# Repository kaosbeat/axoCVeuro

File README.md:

# axoCVeuro

# BOM
https://www.digikey.be/product-detail/en/e-switch/100SP1T1B4M2QE/EG2355-ND/378824

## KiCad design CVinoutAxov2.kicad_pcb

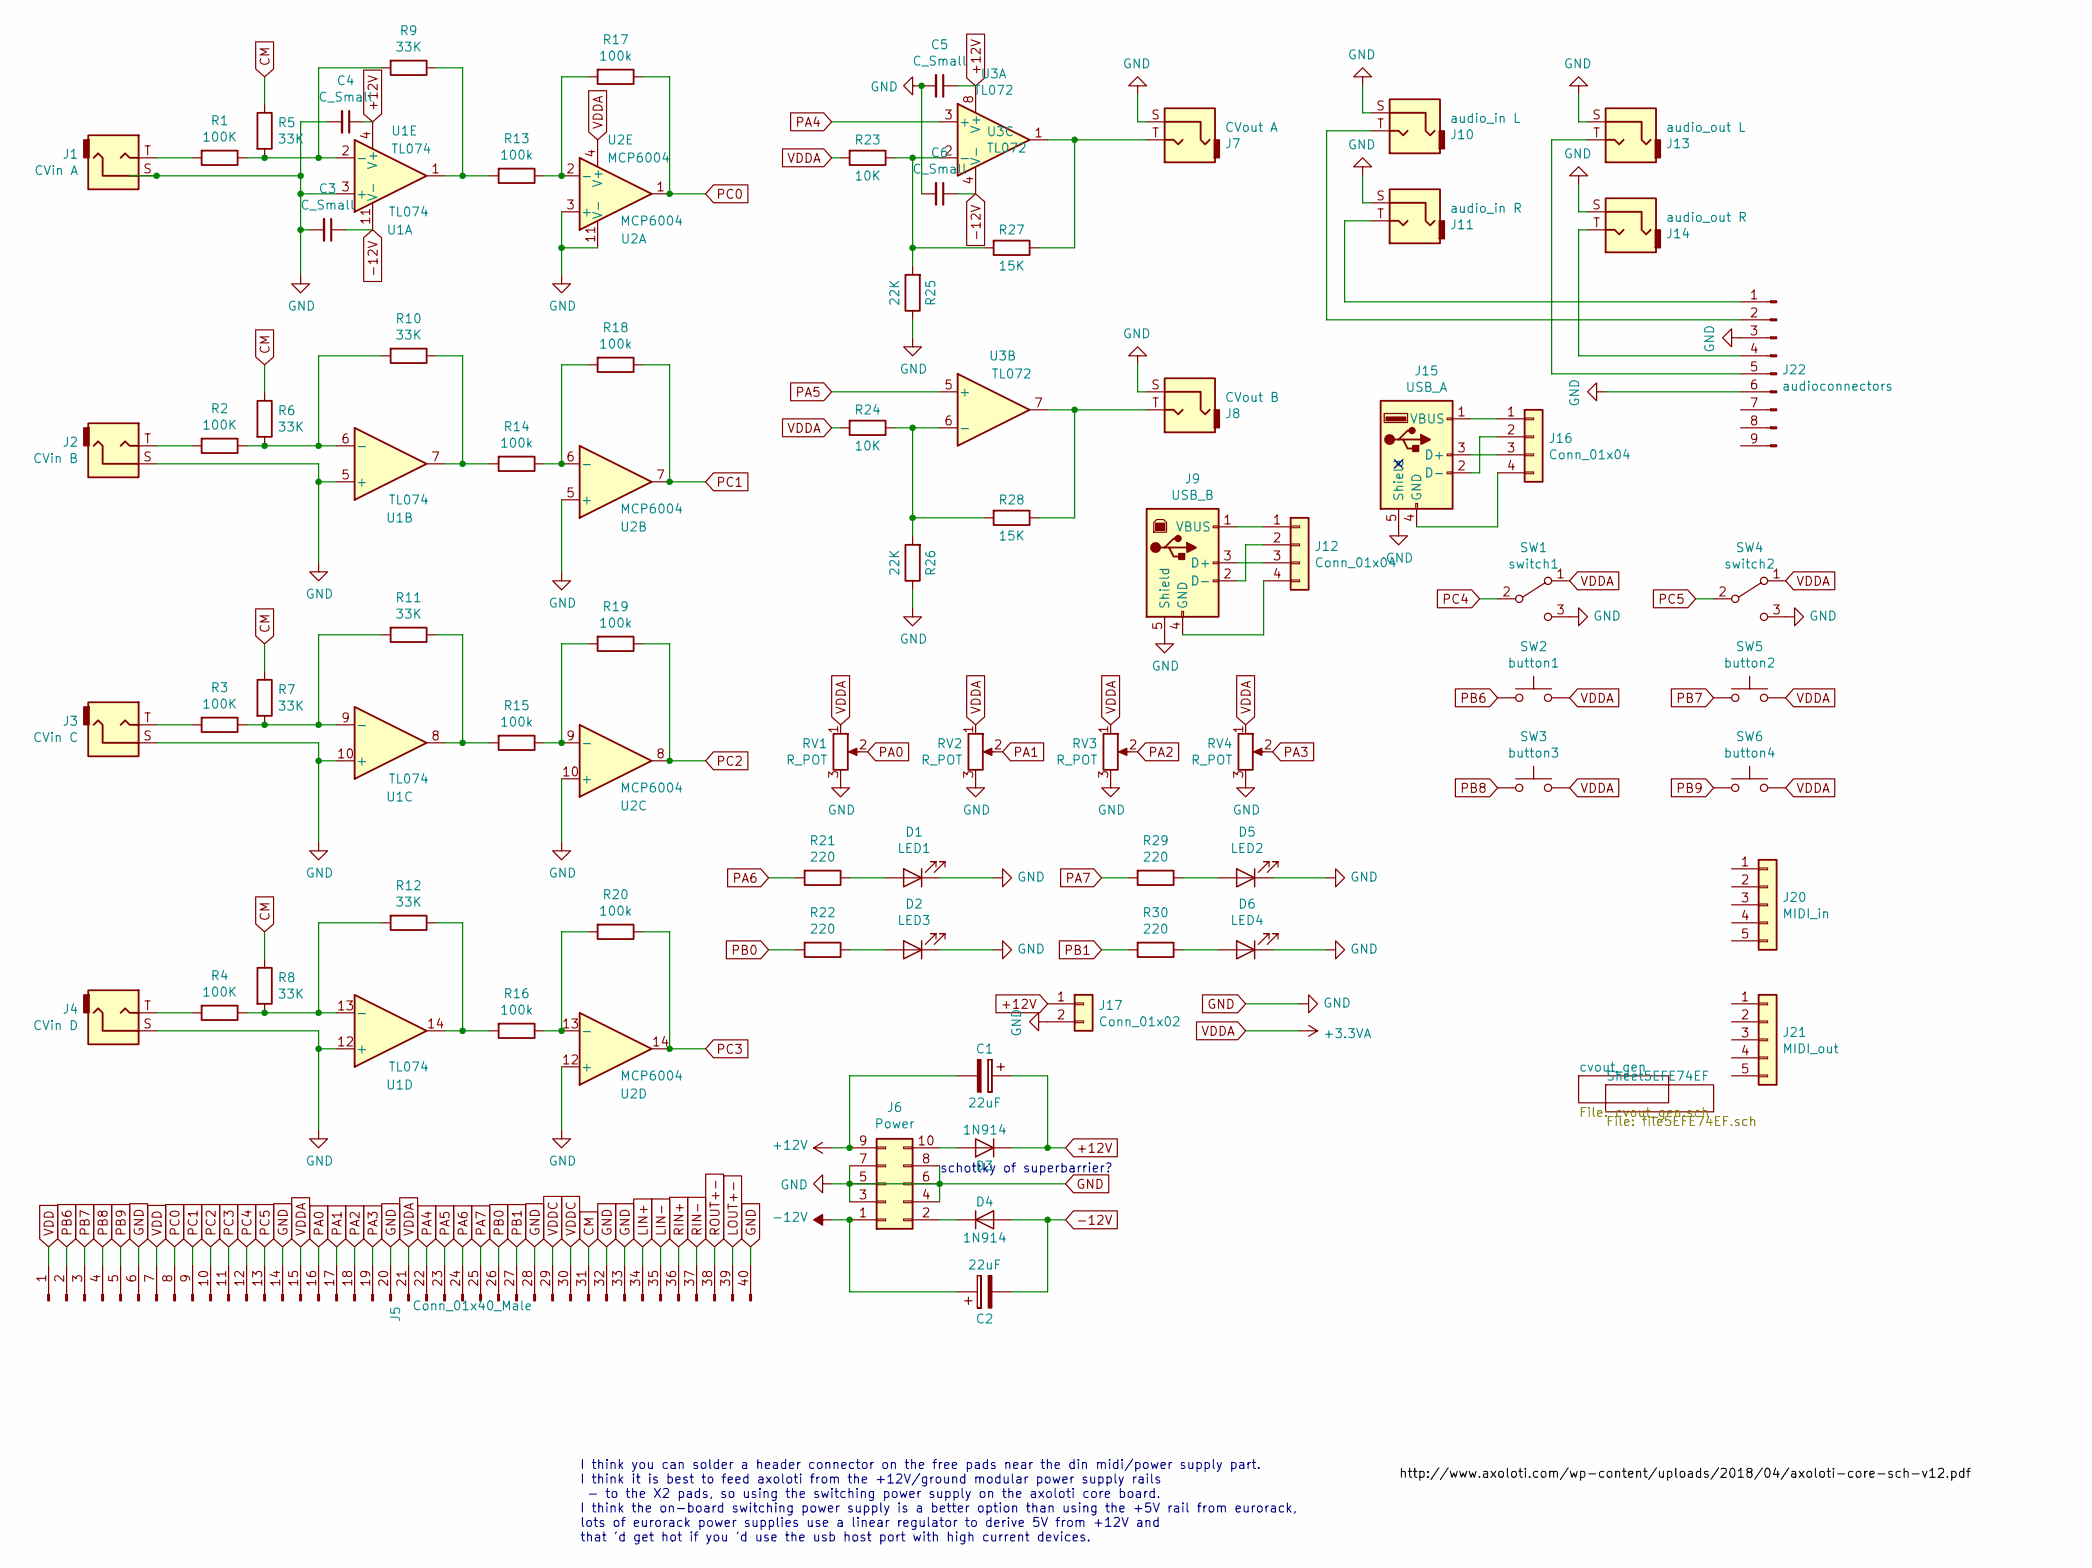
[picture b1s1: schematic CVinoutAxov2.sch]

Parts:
C1, C2: 22uF; CP_Radial_D5.0mm_P2.50mm
C3, C4, C5, C6: C_Small; C_Disc_D5.0mm_W2.5mm_P2.50mm
D1: LED1; LED_D5.0mm
D2: LED3; LED_D5.0mm
D3, D4: 1N914; D_DO-35_SOD27_P7.62mm_Horizontal
D5: LED2; LED_D5.0mm
D6: LED4; LED_D5.0mm
J1: CVin A; Jack_3.5mm_QingPu_WQP-PJ398SM_Vertical_CircularHoles
J2: CVin B; Jack_3.5mm_QingPu_WQP-PJ398SM_Vertical_CircularHoles
J3: CVin C; Jack_3.5mm_QingPu_WQP-PJ398SM_Vertical_CircularHoles
J4: CVin D; Jack_3.5mm_QingPu_WQP-PJ398SM_Vertical_CircularHoles
J5: Conn_01x40_Male; PinHeader_1x40_P2.54mm_Vertical
J6: Power; IDC-Header_2x05_P2.54mm_Vertical
J7: CVout A; Jack_3.5mm_QingPu_WQP-PJ398SM_Vertical_CircularHoles
J8: CVout B; Jack_3.5mm_QingPu_WQP-PJ398SM_Vertical_CircularHoles
J9: USB_B; USB_B_Amphenol_MUSB-D511_Vertical_Rugged
J10: audio_in L; Jack_3.5mm_QingPu_WQP-PJ398SM_Vertical_CircularHoles
J11: audio_in R; Jack_3.5mm_QingPu_WQP-PJ398SM_Vertical_CircularHoles
J12: Conn_01x04; PinHeader_1x04_P2.54mm_Vertical
J13: audio_out L; Jack_3.5mm_QingPu_WQP-PJ398SM_Vertical_CircularHoles
J14: audio_out R; Jack_3.5mm_QingPu_WQP-PJ398SM_Vertical_CircularHoles
J15: USB_A; USB-A-S-VT
J16: Conn_01x04; JST_EH_B04B-EH-A_1x04_P2.50mm_Vertical
J17: Conn_01x02; JST_EH_B02B-EH-A_1x02_P2.50mm_Vertical
J20: MIDI_in; PinHeader_1x05_P2.54mm_Vertical
J21: MIDI_out; PinHeader_1x05_P2.54mm_Vertical
J22: audioconnectors; PinHeader_1x09_P2.54mm_Vertical
R1, R2, R3, R4: 100K; R_Axial_DIN0207_L6.3mm_D2.5mm_P10.16mm_Horizontal
R5, R6, R7, R8, R9, R10, R11, R12: 33K; R_Axial_DIN0207_L6.3mm_D2.5mm_P10.16mm_Horizontal
R13, R14, R15, R16, R17, R18, R19, R20: 100k; R_Axial_DIN0207_L6.3mm_D2.5mm_P10.16mm_Horizontal
R21, R22, R29, R30: 220; R_Axial_DIN0207_L6.3mm_D2.5mm_P10.16mm_Horizontal
R23, R24: 10K; R_Axial_DIN0207_L6.3mm_D2.5mm_P10.16mm_Horizontal
R25, R26: 22K; R_Axial_DIN0207_L6.3mm_D2.5mm_P10.16mm_Horizontal
R27, R28: 15K; R_Axial_DIN0207_L6.3mm_D2.5mm_P10.16mm_Horizontal
RV1, RV2, RV3, RV4: R_POT; Potentiometer_Alps_RK09K_Single_Vertical
SW1: switch1; E-switch_SPDT_100SP1T1B4M2QE
SW2: button1; Push_E-Switch_KS01Q01
SW3: button3; Push_E-Switch_KS01Q01
SW4: switch2; E-switch_SPDT_100SP1T1B4M2QE
SW5: button2; Push_E-Switch_KS01Q01
SW6: button4; Push_E-Switch_KS01Q01
U1: TL074; SMDIP-14_W9.53mm
U2: MCP6004; SMDIP-14_W9.53mm
U3: TL072; SMDIP-8_W9.53mm

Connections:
+12V: C1.1, C1.2, C4.1, C5.1, D3.1 (K), J6.9, J17.1, U1.4 (V+), U3.8 (V+)
-12V: C2.1, C2.2, C3.1, C6.1, D4.2 (A), J6.1, U1.11 (V-), U3.4 (V-)
CM: J5.31, R5.1, R6.1, R7.1, R8.1
GND: C3.2, C4.2, C5.2, C6.2, D1.1 (K), D2.1 (K), D5.1 (K), D6.1 (K), J1.S, J2.S, J3.S, J4.S, J5.6, J5.14, J5.20, J5.28, J5.32, J5.33, J5.40, J6.3, J6.4, J6.5, J6.6, J6.7, J6.8, J7.S, J8.S, J9.5 (Shield), J10.S, J11.S, J13.S, J14.S, J15.5 (Shield), J17.2, J22.3, J22.6, R25.1, R26.1, RV1.3, RV2.3, RV3.3, RV4.3, SW1.3 (C), SW4.3 (C), U1.3 (+), U1.5 (+), U1.10 (+), U1.12 (+), U2.3 (+), U2.5 (+), U2.10 (+), U2.11 (V-), U2.12 (+)
LIN+: J5.34
LIN-: J5.35
LOUT+-: J5.39
unnamed: D1.2 (A), R21.1
unnamed: D2.2 (A), R22.1
unnamed: D3.2 (A), J6.10
unnamed: D4.1 (K), J6.2
unnamed: D5.2 (A), R29.1
unnamed: D6.2 (A), R30.1
unnamed: J1.T, R1.2
unnamed: J2.T, R2.2
unnamed: J3.T, R3.2
unnamed: J4.T, R4.2
unnamed: J7.T, R27.1, U3.1
unnamed: J8.T, R28.1, U3.7
unnamed: J10.T, J22.2
unnamed: J11.T, J22.1
unnamed: J9.1 (VBUS), J12.1
unnamed: J9.2 (D-), J12.2
unnamed: J9.3 (D+), J12.3
unnamed: J9.4 (GND), J12.4
unnamed: J13.T, J22.5
unnamed: J14.T, J22.4
unnamed: J15.1 (VBUS), J16.1
unnamed: J15.2 (D-), J16.2
unnamed: J15.3 (D+), J16.3
unnamed: J15.4 (GND), J16.4
unnamed: R1.1, R5.2, R9.2, U1.2 (-)
unnamed: R10.1, R14.2, U1.7
unnamed: R2.1, R6.2, R10.2, U1.6 (-)
unnamed: R11.1, R15.2, U1.8
unnamed: R3.1, R7.2, R11.2, U1.9 (-)
unnamed: R12.1, R16.2, U1.14
unnamed: R4.1, R8.2, R12.2, U1.13 (-)
unnamed: R13.1, R17.2, U2.2 (-)
unnamed: R9.1, R13.2, U1.1
unnamed: R14.1, R18.2, U2.6 (-)
unnamed: R15.1, R19.2, U2.9 (-)
unnamed: R16.1, R20.2, U2.13 (-)
unnamed: R23.1, R25.2, R27.2, U3.2 (-)
unnamed: R24.1, R26.2, R28.2, U3.6 (-)
PA0: J5.16, RV1.2
PA1: J5.17, RV2.2
PA2: J5.18, RV3.2
PA3: J5.19, RV4.2
PA4: J5.22, U3.3 (+)
PA5: J5.23, U3.5 (+)
PA6: J5.24, R21.2
PA7: J5.25, R29.2
PB0: J5.26, R22.2
PB1: J5.27, R30.2
PB6: J5.2, SW2.1
PB7: J5.3, SW5.1
PB8: J5.4, SW3.1
PB9: J5.5, SW6.1
PC0: J5.8, R17.1, U2.1
PC1: J5.9, R18.1, U2.7
PC2: J5.10, R19.1, U2.8
PC3: J5.11, R20.1, U2.14
PC4: J5.12, SW1.2 (B)
PC5: J5.13, SW4.2 (B)
RIN+: J5.36
RIN-: J5.37
ROUT+-: J5.38
VDD: J5.1, J5.7
VDDA: J5.15, J5.21, R23.2, R24.2, RV1.1, RV2.1, RV3.1, RV4.1, SW1.1 (A), SW2.2, SW3.2, SW4.1 (A), SW5.2, SW6.2, U2.4 (V+)
VDDC: J5.29, J5.30

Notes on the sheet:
I think you can solder a header connector on the free pads near the din midi/power supply part. I think it is best to feed axoloti from the +12V/ground modular power supply rails - to the X2 pads, so using the switching power supply on the axoloti core board. I think the on-board switching power su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
schottky of superbarrier?

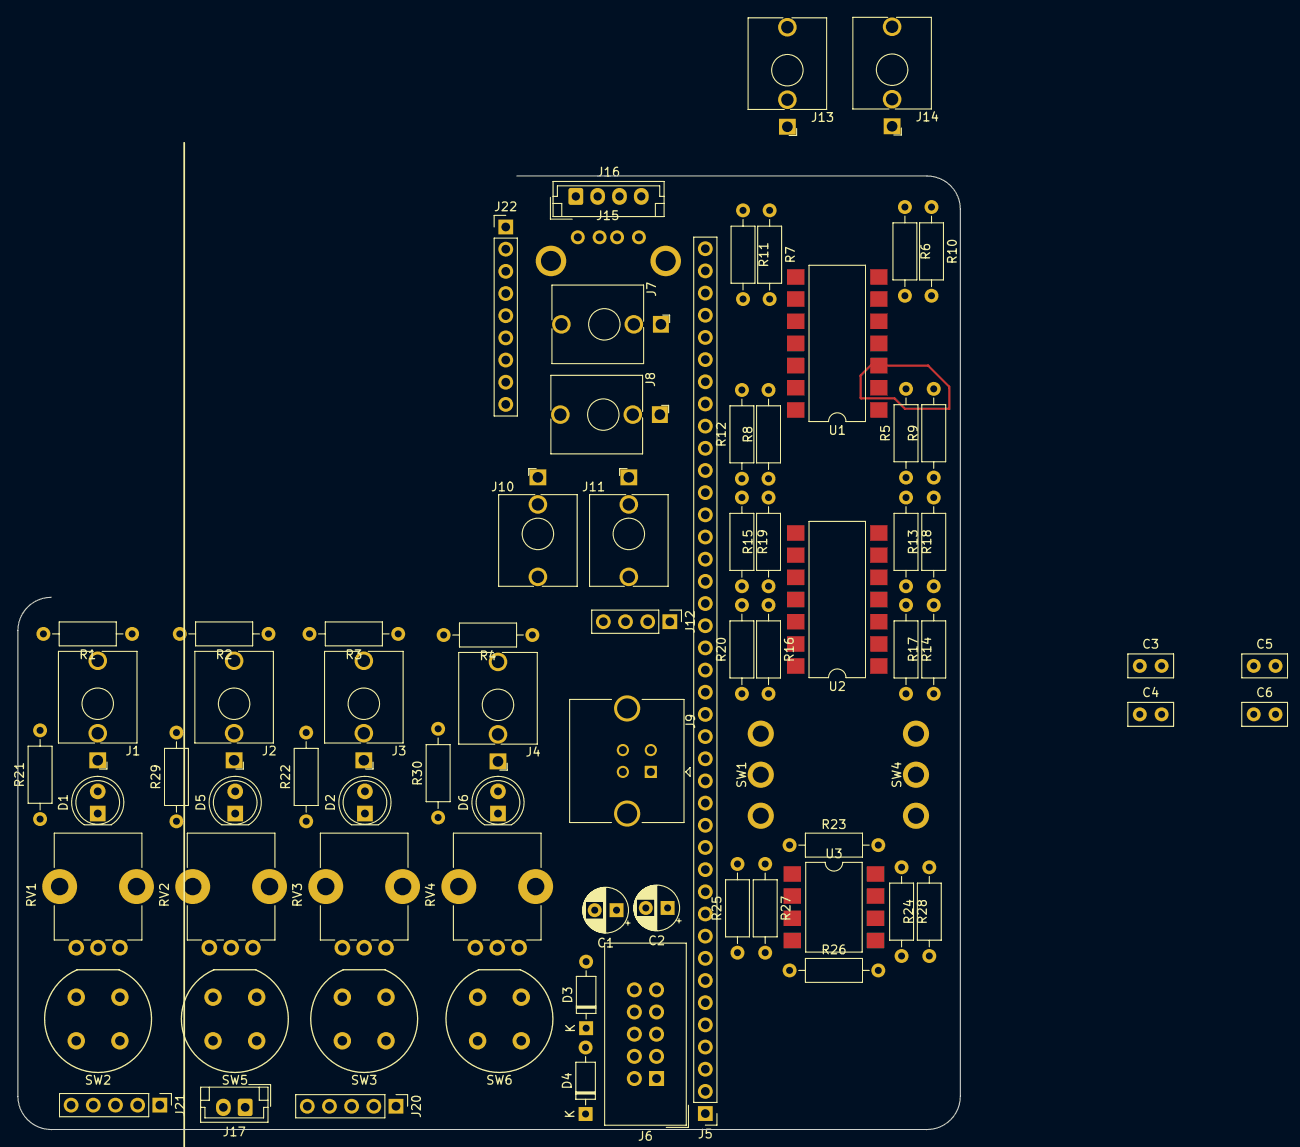
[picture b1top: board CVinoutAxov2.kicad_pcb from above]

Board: 2 copper layers, 108.0 x 109.2 mm, 75 parts (0 on the bottom side), 65 nets.

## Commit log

2020-07-02 low-offset version
2020-07-02 added disc caps
